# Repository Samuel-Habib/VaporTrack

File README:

dependencies: arm-none-eabi-gcc, ninja, cmake, stlink
,
init: cmake --preset Debug
cmake --build build --preset Debug --target flash
st-flash --reset write build/debug/vapor_track.bin 0x08000000

nvim optional: ln -s build/compile_commands.json .

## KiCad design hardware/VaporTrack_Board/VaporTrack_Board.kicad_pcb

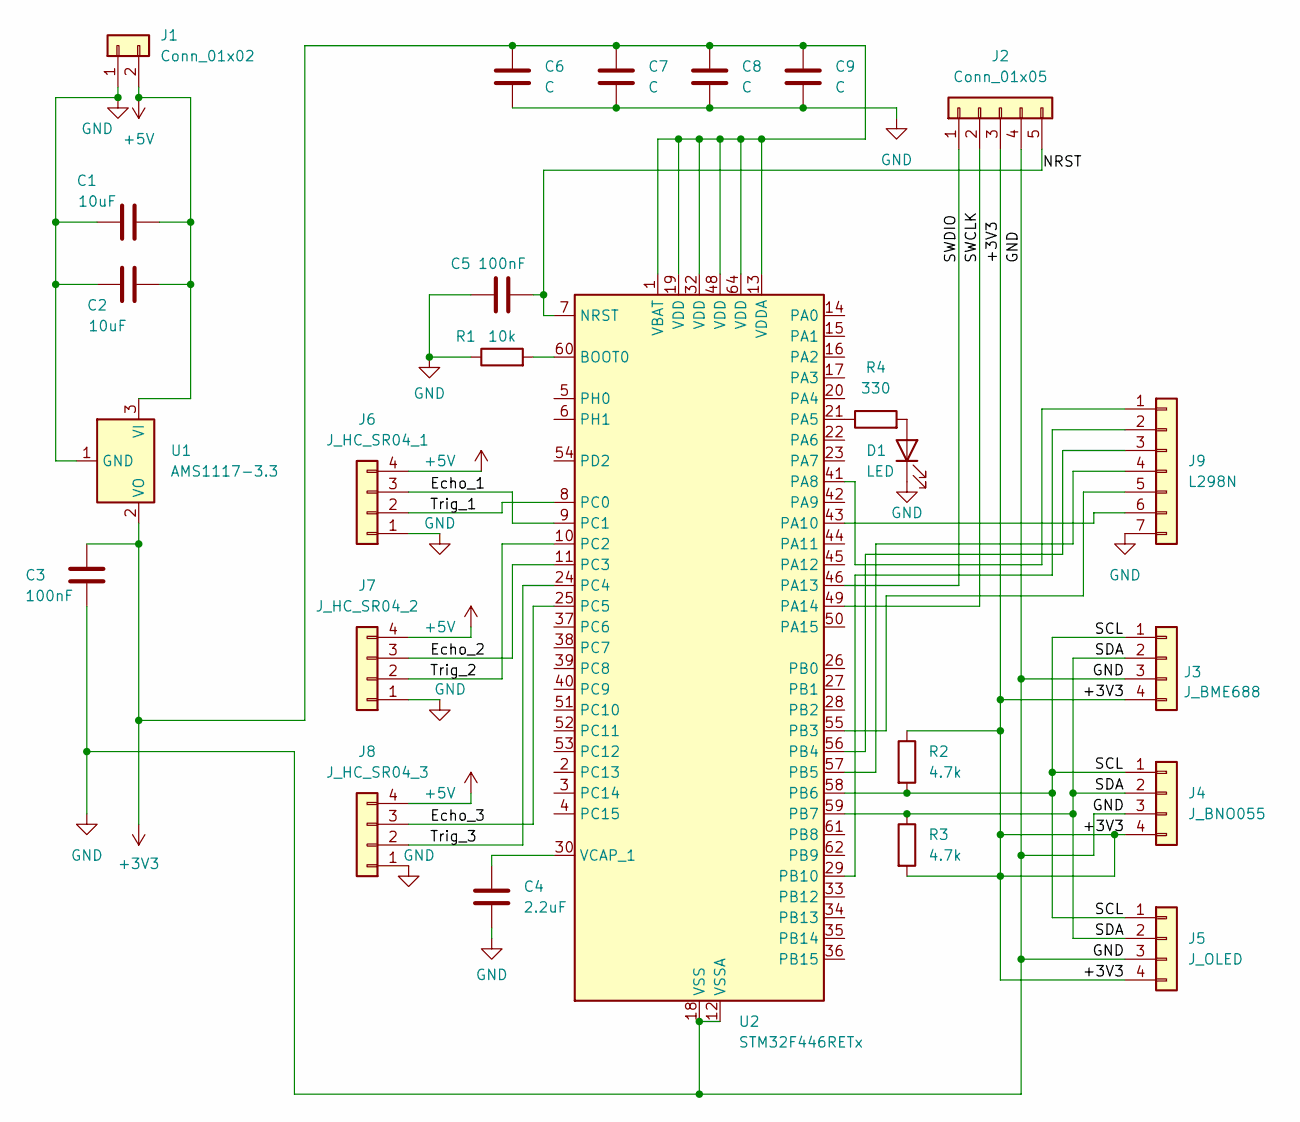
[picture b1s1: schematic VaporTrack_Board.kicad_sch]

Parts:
C1, C2: 10uF; C_0805_2012Metric
C3, C5: 100nF; C_0805_2012Metric
C4: 2.2uF; C_0805_2012Metric
C6, C7, C8, C9: C; C_0805_2012Metric
D1: LED; LED_0805_2012Metric
J1: Conn_01x02; PinHeader_1x02_P2.54mm_Vertical
J2: Conn_01x05; PinHeader_1x05_P2.54mm_Vertical
J3: J_BME688; PinHeader_1x04_P2.54mm_Vertical
J4: J_BNO055; PinHeader_1x04_P2.54mm_Vertical
J5: J_OLED; PinHeader_1x04_P2.54mm_Vertical
J6: J_HC_SR04_1; PinHeader_1x04_P2.54mm_Vertical
J7: J_HC_SR04_2; PinHeader_1x04_P2.54mm_Vertical
J8: J_HC_SR04_3; PinHeader_1x04_P2.54mm_Vertical
J9: L298N; PinHeader_1x07_P2.54mm_Vertical
R1: 10k; R_0805_2012Metric
R2, R3: 4.7k; R_0805_2012Metric
R4: 330; R_0805_2012Metric
U1: AMS1117-3.3; SOT-223-3_TabPin2
U2: STM32F446RETx; LQFP-64_10x10mm_P0.5mm

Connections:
+3V3: C3.1, C6.1, C7.2, C8.2, C9.1, J2.3, J3.4, J4.4, J5.4, R2.1, R3.2, U1.2 (VO), U2.1 (VBAT), U2.13 (VDDA), U2.19 (VDD), U2.32 (VDD), U2.48 (VDD), U2.64 (VDD)
+5V: C1.2, C2.2, J1.2, J6.4, J7.4, J8.4, U1.3 (VI)
/Echo_1: J6.3, U2.9 (PC1)
/Echo_2: J7.3, U2.11 (PC3)
/Echo_3: J8.3, U2.25 (PC5)
/NRST: C5.1, J2.5, U2.7 (NRST)
/SCL: J3.1, J4.1, J5.1, R2.2, U2.58 (PB6)
/SDA: J3.2, J4.2, J5.2, R3.1, U2.59 (PB7)
/SWCLK: J2.2, U2.49 (PA14)
/SWDIO: J2.1, U2.46 (PA13)
/Trig_1: J6.2, U2.8 (PC0)
/Trig_2: J7.2, U2.10 (PC2)
/Trig_3: J8.2, U2.24 (PC4)
GND: C1.1, C2.1, C3.2, C4.2, C5.2, C6.2, C7.1, C8.1, C9.2, D1.1 (K), J1.1, J2.4, J3.3, J4.3, J5.3, J6.1, J7.1, J8.1, J9.7, R1.1, U1.1 (GND), U2.12 (VSSA), U2.18 (VSS), U2.31 (VSS), U2.47 (VSS), U2.63 (VSS)
unnamed: D1.2 (A), R4.2
unnamed: J9.1, U2.41 (PA8)
unnamed: J9.2, U2.29 (PB10)
unnamed: J9.3, U2.56 (PB4)
unnamed: J9.4, U2.57 (PB5)
unnamed: J9.5, U2.55 (PB3)
unnamed: J9.6, U2.43 (PA10)
unnamed: R1.2, U2.60 (BOOT0)
unnamed: R4.1, U2.21 (PA5)
unnamed: C4.1, U2.30 (VCAP_1)

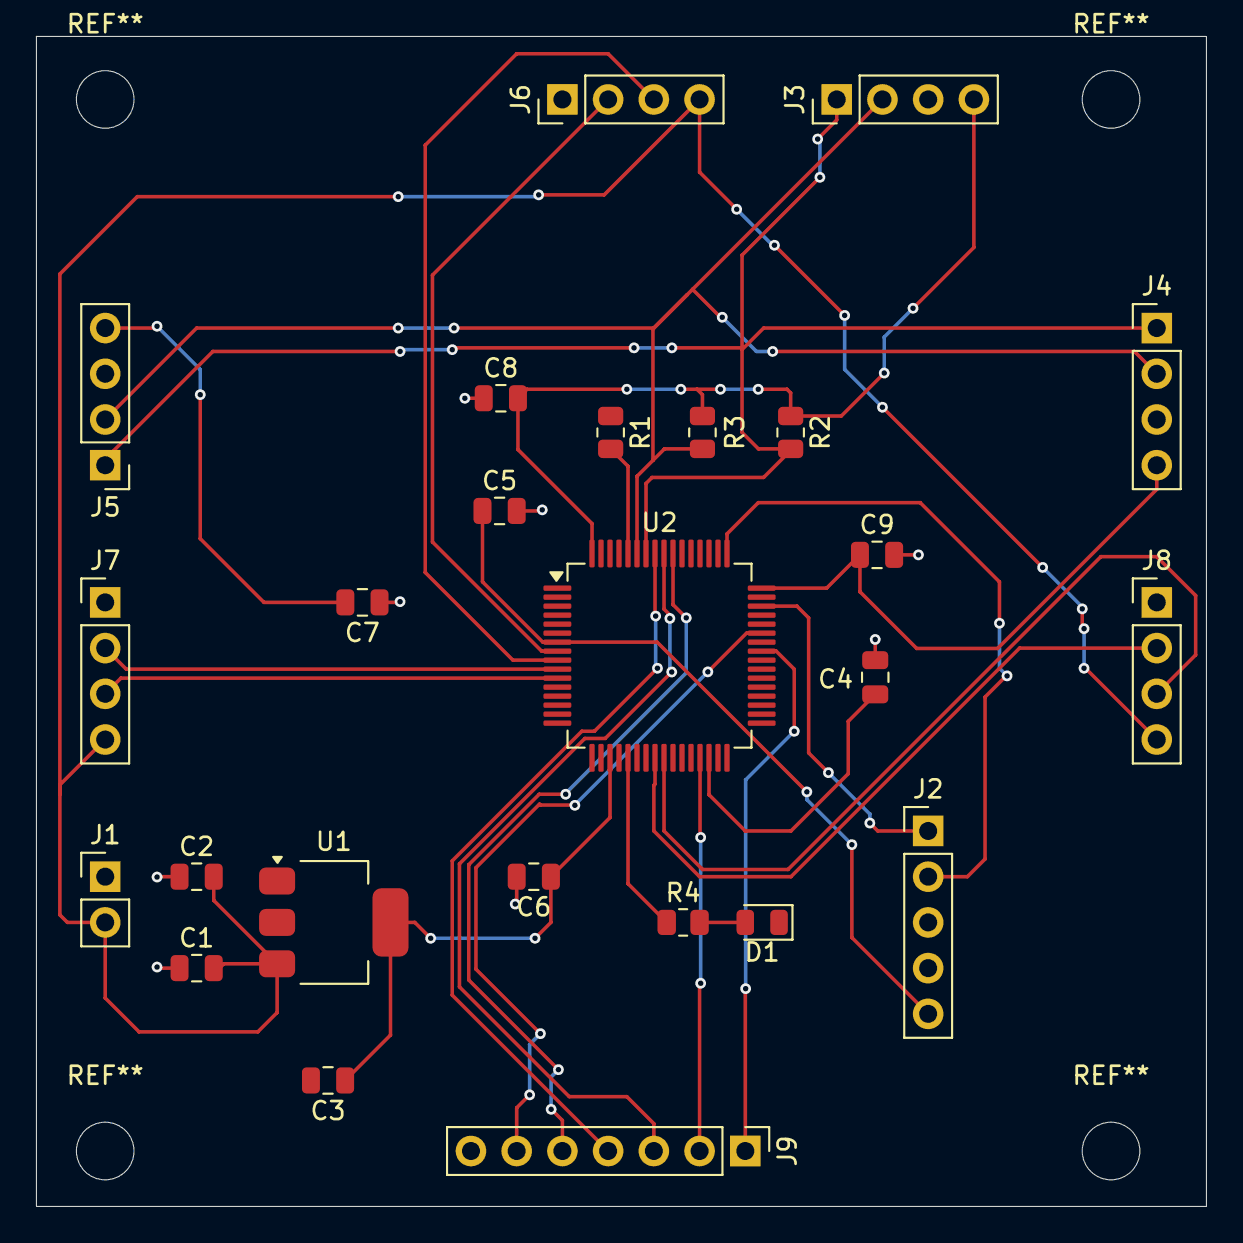
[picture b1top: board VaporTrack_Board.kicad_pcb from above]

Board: 2 copper layers, 65.0 x 65.0 mm, 25 parts (0 on the bottom side), 24 nets.

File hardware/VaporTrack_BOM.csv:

Item,Designator,Qty,Value,Package,Description,Suggested MPN,DigiKey Example
1,"C1, C2",2,10uF,0805,Capacitor 10uF 16V X7R 0805,CL21A106KOQNNNE,
2,"C3, C5, C6, C7, C8, C9",6,100nF,0805,Capacitor 0.1uF 50V X7R 0805,CL21B104KBCNNNC,
3,C4,1,2.2uF,0805,Capacitor 2.2uF 16V X7R 0805 (VCAP),CL21B225KOFNNNE,
4,R1,1,10k,0805,Resistor 10k 5% 0805 (BOOT0),RC0805JR-0710KL,
5,"R2, R3",2,4.7k,0805,Resistor 4.7k 5% 0805 (I2C Pullup),RC0805JR-074K7L,
6,R4,1,330,0805,Resistor 330 ohm 5% 0805 (LED),RC0805JR-07330RL,
7,D1,1,LED,0805,LED Green/Red 0805,,
8,U1,1,AMS1117-3.3,SOT-223,LDO Voltage Regulator 3.3V 1A,,
9,U2,1,STM32F446RET6,LQFP-64,MCU ARM Cortex-M4 180MHz 512KB Flash,,
10,J1,1,2-pin Header,2.54mm TH,Pin Header 1x02 2.54mm,,
11,J2,1,5-pin Header,2.54mm TH,SWD Debug Header 1x05 2.54mm,,
12,"J3, J4, J5, J6, J7, J8",6,4-pin Header,2.54mm TH,Sensor Headers 1x04 2.54mm,,
13,J9,1,7-pin Header,2.54mm TH,Motor Driver Header 1x07 2.54mm,,

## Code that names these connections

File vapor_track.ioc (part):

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Mcu.Name=STM32F446R(C-E)Tx
Mcu.Package=LQFP64
Mcu.UserName=STM32F446RETx
PA10.GPIOParameters=GPIO_Label
PA10.GPIO_Label=ENB
PA10.Signal=S_TIM1_CH3
PA13.Mode=Serial_Wire
PA13.Signal=SYS_JTMS-SWDIO
PA14.Mode=Serial_Wire
PA14.Signal=SYS_JTCK-SWCLK
PA5.GPIOParameters=GPIO_Label
PA5.GPIO_Label=LED
PA5.Signal=S_TIM2_CH1_ETR
PA8.GPIOParameters=GPIO_Label
PA8.GPIO_Label=ENA
PA8.Signal=S_TIM1_CH1
PB10.GPIOParameters=GPIO_Label
PB10.GPIO_Label=IN1
PB10.Signal=GPIO_Output
PB3.GPIOParameters=GPIO_Label
PB3.GPIO_Label=IN4
PB3.Signal=GPIO_Output
PB4.GPIOParameters=GPIO_Label
PB4.GPIO_Label=IN2
PB4.Signal=GPIO_Output
PB5.GPIOParameters=GPIO_Label
PB5.GPIO_Label=IN3
PB5.Signal=GPIO_Output
PB6.Mode=I2C
PB6.Signal=I2C1_SCL
PB7.Mode=I2C
PB7.Signal=I2C1_SDA
RCC.SYSCLKFreq_VALUE=180000000
RCC.SYSCLKSource=RCC_SYSCLKSOURCE_PLLCLK
board=custom

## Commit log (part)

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2025-12-08 init: initial project setup from STM32CubeMX with FreeRTOS and CMake
2025-12-16 motor: implement L298N dual H-bridge driver with TIM1 PWM
2025-12-23 motor: add speed clamping, direction logic, and active braking
2026-01-08 timer: configure TIM4 prescaler for 1MHz microsecond timebase
2026-01-17 hcsr04: add 3-channel ultrasonic distance ranging driver
2026-01-24 hcsr04: implement sequential triggering and echo timeout handling
2026-02-03 imu: add BNO055 9-DOF driver for NDOF Euler heading acquisition
2026-02-12 display: add SSD1306 128x64 OLED driver with framebuffer and font
2026-02-19 bme688: implement forced-mode gas sensor driver with compensation formulas
2026-02-28 sensors: centralize telemetry state with FreeRTOS mutex synchronization
2026-02-28 Add schematic and PCB layout images to README
2026-02-28 hardware: add KiCad PCB and schematic files to repo
2026-02-28 hardware: update 3D model paths from KiCad 6 to KiCad 7
2026-02-28 hardware: flatten directory structure for cleaner repository layout
2026-02-28 docs: simplify complex LaTeX equations to code blocks for compatibility
2026-03-07 mapping: implement dead-reckoned spatial coordinate and gas sample buffer
2026-03-15 mapping: compute 2D planar gas gradient using weighted least-squares
2026-03-24 nav: add finite state machine with ultrasonic obstacle override
2026-03-29 rtos: integrate 6-task scheduling loop, task priorities, and heartbeat PWM
2026-03-31 motor pwm working
2026-04-01 left right
2026-04-01 cleanup
2026-04-04 docs: add system architecture, pinout map, and bench test guide to README
